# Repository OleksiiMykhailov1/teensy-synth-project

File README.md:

# Teensy synth project

_Listen on YouTube_

This is a project I was working on in 2023. My main goal was to create an interesting object to interact with while learning about software and hardware development. Before starting it, 
I did some small projects with Arduino and assembled a small analogue synth with 3 voices and a low-pass filter. I found the programming part more interesting to me, and it allowed more to be done.
Teensy 3.6 was chosen because it works with the Audio Library and Audio Systems Design Tool, which allow me to work on system design while relying on a professionally written DSP and an easy-to-use design tool to create an audio patch for my synthesizer.
The first version of the project was soldered on a perfboard, as a proof of concept. It worked, so I decided to try to design and manufacture a PCB.

_Perfboard and a PCB versions_

## Hardware
 
| Part | Details |
|------|---------|
| Microcontroller | Teensy 3.6 |
| Display | ILI9341 TFT (320×240, landscape) |
| Keypad | 5×4 matrix of Kailh Choc V1 Low Profile Switches |
| Rotary encoder | to navigate through the menu |
| Audio out | USB audio; the SGTL5000 codec on board was not working, and I was not able to find out why at the time |
| Power | powered through USB |

## Features
 
- **4-voice polyphony**, with 4 operators per voice 
- **11 FM algorithms**, selectable from the display
- **Per-operator controls:** waveform (sine/triangle/square), frequency ratio, level and a full ADSR envelope
- **Effects chain:** low-pass filter with LFO, multi-tap delay with feedback, and Freeverb reverb, each with its own wet/dry mix
- **Step Sequencer:** up to 32 steps, with rests and adjustable BPM
- **On-screen feedback:** algorithm diagram, envelope graphs for every operator and a live output waveform

## How it works
Each voice has 4 operators, each a frequency-modulated oscillator followed by its own ADSR envelope. A mixer in front of every oscillator chooses which operators modulate it.
Then the signal goes through the voice mixer, through the effects, and to one of the outputs.

### Keypad layout
 
 | | Col 1 | Col 2 | Col 3 | Col 4 | Col 5 |
|---|:---:|:---:|:---:|:---:|:---:|
| **Row 1** | Edit / confirm | F♯  | D♯ | C♯| Next |
| **Row 2** | F| E | D | C | Back |
| **Row 3** |Seq play/stop | C♯(+1 oct) | A♯ |  G♯ | - |
| **Row 4** |  C (+1 oct) | B | A  | G | - |

- **Notes:** up to 4 notes can sound at once; each new note takes the next free voice.
- **Next / Back:** switch screens, or step through parameters while editing.
- **Edit / confirm:** enter or leave editing for the highlighted item.
- **Seq play/stop:** starts or stops the sequencer from any screen.
  
### Screens

Use **Next / Back** (when not editing) to move between screens.
 
**1. Synth.** Turn the encoder to highlight **OCT**, **ALG** or **OP-1 … OP-4**, then press **Edit** to change it.
For an operator, **Next / Back** step through the parameter being edited, and the encoder changes its value:
 
| Parameter | Range |
|-----------|-------|
| Attack | 0–1000 ms |
| Decay | 0–1000 ms |
| Sustain | 0.0–1.0 |
| Release | 0–3800 ms |
| Ratio | 0–16 (frequency multiple of the played note) |
| Level | 0.0–1.0 |
| Waveform | sine / triangle / square |
 
**2. Effects.** Pick **Reverb**, **Delay** or **Filter** with the encoder, press **Edit**, use **Next / Back** to move the arrow between parameters and the encoder to change them:
 
| Block | Parameters |
|-------|------------|
| Reverb | room size (0–1), damping (0–1), wet/dry |
| Delay | taps (0–3), time (10–500 ms), feedback (0–0.5), wet/dry |
| Filter | cutoff (0–5000 Hz), resonance, wet/dry, LFO rate (0–50 Hz) |
 
**3. Step Sequencer.** Pick **Record**, **Steps** or **BPM** with the encoder:
 
- **Record:** press **Edit** to start/stop recording. Play notes to write them into the sequence; **Next / Back** write a rest.
- **Steps:** sequence length, 1–32.
- **BPM:** tempo of the step clock.
- The Sequencer plays on a single voice (monophonic).

### Project problems

- SGTL5000 codec. While I was working on a project, there was a chip shortage, and I was only able to buy it from a sketchy AliExpress supplier. Either this or my poor, at the time, soldering skills, I was not able to make it work, and USB was the only audio output that was working.
- Code. It was my first attempt to do something complex. I had no experience and made a lot of bad design choices, but it somehow works, which is cool.
- PCB. Besides a problem with a codec, it's also my first PCB, routing is bad and probably anyone with any experience will find a lot of mistakes.

### Planned upgrades

At some point, I decided that the PCB needs serious upgrades, and there is no point in continuing to write code if I will make major changes to the hardware.
You can see files for the upgraded PCB in [`PCB files/teensy_4_1_pcb/`](PCB%20files/teensy_4_1_pcb/).
What was made:
- I decided to switch from a display module to a bare screen. It allowed me to reduce the synth's size.
- I removed 5 keys. In the last design, part of the keys were not used at all, which again reduced the size.
- SGTL5000 was changed to PT8211, it's easier to use, cheaper, and good enough for my tasks.
- Added battery support. I copied this part of the schematic from another synth that used a Teensy.

This board was never manufactured. At the time, I changed jobs, and there was no time to continue work on it.

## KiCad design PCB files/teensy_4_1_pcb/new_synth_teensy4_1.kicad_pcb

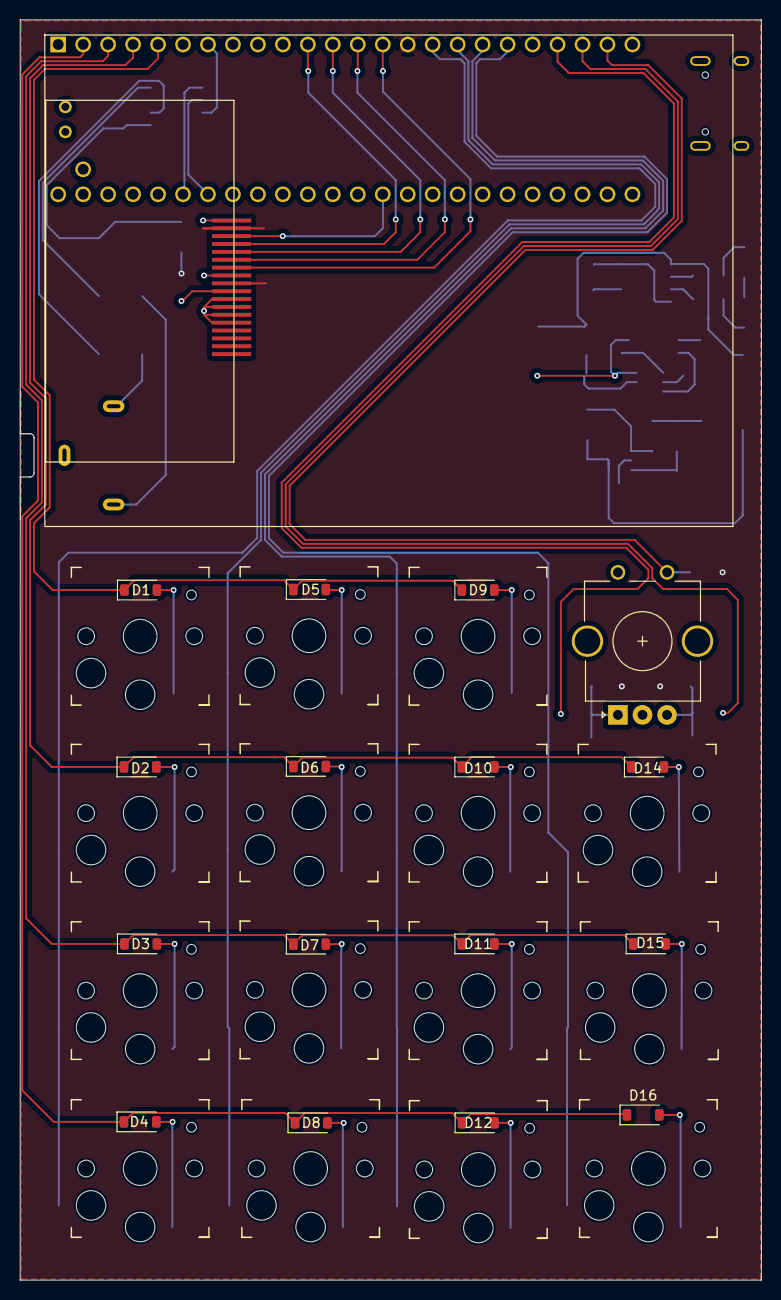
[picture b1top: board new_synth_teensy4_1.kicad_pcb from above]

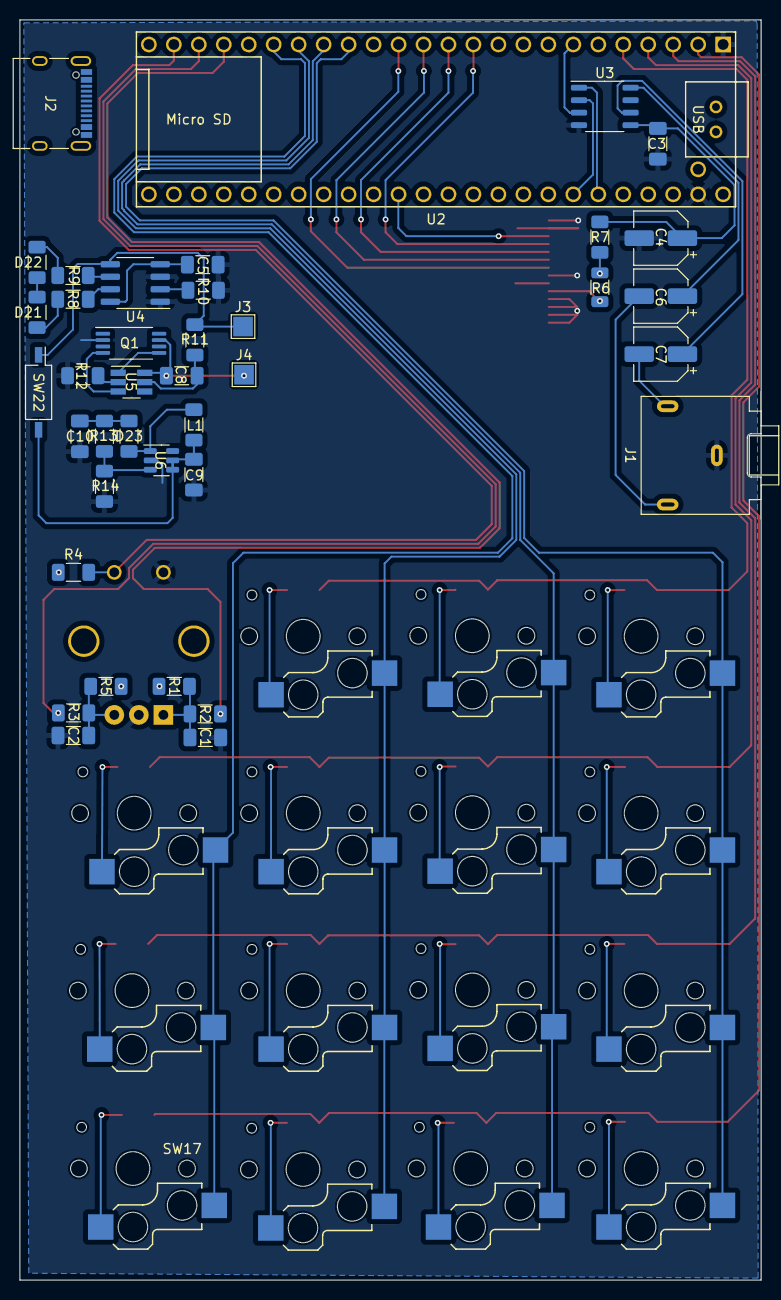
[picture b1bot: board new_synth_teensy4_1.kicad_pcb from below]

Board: 2 copper layers, 75.4 x 128.2 mm, 71 parts (39 on the bottom side), 61 nets.

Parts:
C1, C2: 100nF; C_1206_3216Metric_Pad1.33x1.80mm_HandSolder
C3: 0.1uF; C_1206_3216Metric_Pad1.33x1.80mm_HandSolder
C4, C6, C7: 47uF; CP_Elec_5x5.8
C5: 10uf; C_1206_3216Metric_Pad1.33x1.80mm_HandSolder
C8: 0.1uf; C_1206_3216Metric_Pad1.33x1.80mm_HandSolder
C9, C10: 22uf; C_1206_3216Metric_Pad1.33x1.80mm_HandSolder
D1, D2, D3, D4, D5, D6, D7, D8, D9, D10, D11, D12, D14, D15, D16: 1N4001; D_SOD-123
D21: RED; R_1206_3216Metric_Pad1.30x1.75mm_HandSolder
D22: GREEN; R_1206_3216Metric_Pad1.30x1.75mm_HandSolder
D23: D_Schottky; R_1206_3216Metric_Pad1.30x1.75mm_HandSolder
J1: AudioJack2_Ground; Jack_3.5mm_CUI_SJ1-3523N_Horizontal
J2: USB_B_Micro; USB_C_Receptacle_XKB_U262-16XN-4BVC11
J3: BAT+ Pad; TestPoint_Pad_2.0x2.0mm
J4: BAT- Pad; TestPoint_Pad_2.0x2.0mm
L1: 22UH; R_1206_3216Metric_Pad1.30x1.75mm_HandSolder
Q1: TSSOP-8_4.4x3mm_P0.65mm
R1, R2, R3, R4, R5: 10K; R_1206_3216Metric_Pad1.30x1.75mm_HandSolder
R6: 1k?; R_1206_3216Metric
R7: 10R; R_1206_3216Metric_Pad1.30x1.75mm_HandSolder
R8, R9: 1K; R_1206_3216Metric_Pad1.30x1.75mm_HandSolder
R10, R12: 2K; R_1206_3216Metric_Pad1.30x1.75mm_HandSolder
R11: r100; R_1206_3216Metric_Pad1.30x1.75mm_HandSolder
R13: 7.5k; R_1206_3216Metric_Pad1.30x1.75mm_HandSolder
R14: 1k; R_1206_3216Metric_Pad1.30x1.75mm_HandSolder
SW1: RotaryEncoder_Switch; RotaryEncoder_Alps_EC11E_Vertical_H20mm_CircularMountingHol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
SW2, SW3, SW4, SW5, SW6, SW7, SW8, SW9, SW10, SW11, SW12, SW13, SW15, SW16, SW17: SW_Push; Kailh_socket_PG1350
SW22: SW_DIP_x01; SW_DIP_SPSTx01_Slide_Copal_CHS-01B_W7.62mm_P1.27mm
U2: Teensy4.1; Teensy41
U3: SOP-8_3.9x4.9mm_P1.27mm
U4: TP4056; SOP-8_3.76x4.96mm_P1.27mm
U5: SOT-23-6_Handsoldering
U6: MT3608; SOT-23-6
U7: ILI9341_BARE_18PIN

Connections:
5V BAT: C10.2, D23.1 (K), R13.2
+3.3V: R1.2, R4.1, R5.1, R6.1, R7.2, U2.15 (3V3), U7.2 (Reset), U7.9 (VCC)
DIN: U2.7 (5_IN2), U3.3 (DIN)
GND: C1.2, C2.1, C3.2, C4.2, C5.2, C9.1, C10.1, J1.G, Q1.2 (S1), R10.1, R12.1, R14.1, SW1.C, SW1.S1, U2.1 (GND), U2.47 (GND), U3.4 (GND), U4.1 (Temp), U4.3 (GND), U6.2 (GND), U7.1 (GND), U7.8 (GND), U7.11 (K1(LED_Cathode)), U7.12 (K2(LED_Cathode)), U7.13 (K3(LED_Cathode)), U7.14 (K4(LED_Cathode))
unnamed: C1.1, R1.1, R2.2, SW1.A
unnamed: C2.2, R3.2, R5.2, SW1.B
unnamed: C6.2, J1.S
unnamed: C7.2, J1.T
unnamed: D1.2 (A), SW2.1
unnamed: D1.1 (K), D5.1 (K), D9.1 (K), U2.5 (3_LRCLK2)
unnamed: D2.2 (A), SW3.1
unnamed: D3.2 (A), SW4.1
unnamed: D4.2 (A), SW5.1
unnamed: D5.2 (A), SW6.1
unnamed: D6.2 (A), SW7.1
unnamed: D7.2 (A), SW8.1
unnamed: D8.2 (A), SW9.1
unnamed: D9.2 (A), SW10.1
unnamed: D10.2 (A), SW11.1
unnamed: D2.1 (K), D6.1 (K), D10.1 (K), D14.1 (K), U2.4 (2_OUT2)
unnamed: D11.2 (A), SW12.1
unnamed: D3.1 (K), D7.1 (K), D11.1 (K), D15.1 (K), U2.3 (1_TX1_CTX2_MISO1)
unnamed: D12.2 (A), SW13.1
unnamed: D4.1 (K), D8.1 (K), D12.1 (K), D16.1 (K), U2.2 (0_RX1_CRX2_CS1)
unnamed: D14.2 (A), SW15.1
unnamed: D15.2 (A), SW16.1
unnamed: D16.2 (A), SW17.1
unnamed: D21.2 (A), D22.2 (A)
unnamed: D21.1 (K), R8.2
unnamed: D22.1 (K), R9.2
unnamed: D23.2 (A), L1.2, U6.1 (SW)
unnamed: C5.1, U4.4 (VCC), U4.8 (CE)
unnamed: J3.1, R11.1, SW22.1, U4.5 (BAT)
unnamed: C8.1, J4.1, Q1.7 (S2), U5.6 (GND)
unnamed: Q1.4 (G1), U5.3 (OC)
unnamed: Q1.5 (G2), U5.1 (OD)
unnamed: U2.11 (9_OUT1C), U7.4 (DC/RS)
unnamed: U2.12 (10_CS_MQSR), U7.5 (CS)
unnamed: U2.13 (11_MOSI_CTX1), U7.6 (SDA(MOSI))
unnamed: U2.14 (12_MISO_MQSL), U7.7 (SDO(MISO))
unnamed: U2.42 (20_A6_TX5_LRCLK1), U3.2 (WS)
unnamed: U2.43 (21_A7_RX5_BCLK1), U3.1 (BCK)
unnamed: SW2.2, SW3.2, SW4.2, SW5.2, U2.16 (24_A10_TX6_SCL2)
unnamed: SW6.2, SW7.2, SW8.2, SW9.2, U2.17 (25_A11_RX6_SDA2)
unnamed: SW10.2, SW11.2, SW12.2, SW13.2, U2.18 (26_A12_MOSI1)
unnamed: SW15.2, SW16.2, SW17.2, U2.19 (27_A13_SCK1)
unnamed: R2.1, U2.21 (29_TX7)
unnamed: R3.1, U2.22 (30_CRX3)
unnamed: R4.2, SW1.S2, U2.23 (31_CTX3)
unnamed: C3.1, C4.1, R7.1, U3.5 (3.3)
unnamed: C7.1, U3.6 (LLCH)
unnamed: C6.1, U3.8 (RCH)
unnamed: R8.1, U4.7 (CHRG)
unnamed: R10.2, U4.2 (Prog)
unnamed: R9.1, U4.6 (STDBY)
unnamed: R12.2, U5.2 (CS)
unnamed: C8.2, R11.2, U5.5 (VCC)
unnamed: C9.2, L1.1, SW22.2, U6.4 (EN), U6.5 (IN)
unnamed: R13.1, R14.2, U6.3 (FB)
unnamed: R6.2, U7.10 (A(LED_Anode))
SCK: U2.35 (13_SCK_LED), U7.3 (SCL)

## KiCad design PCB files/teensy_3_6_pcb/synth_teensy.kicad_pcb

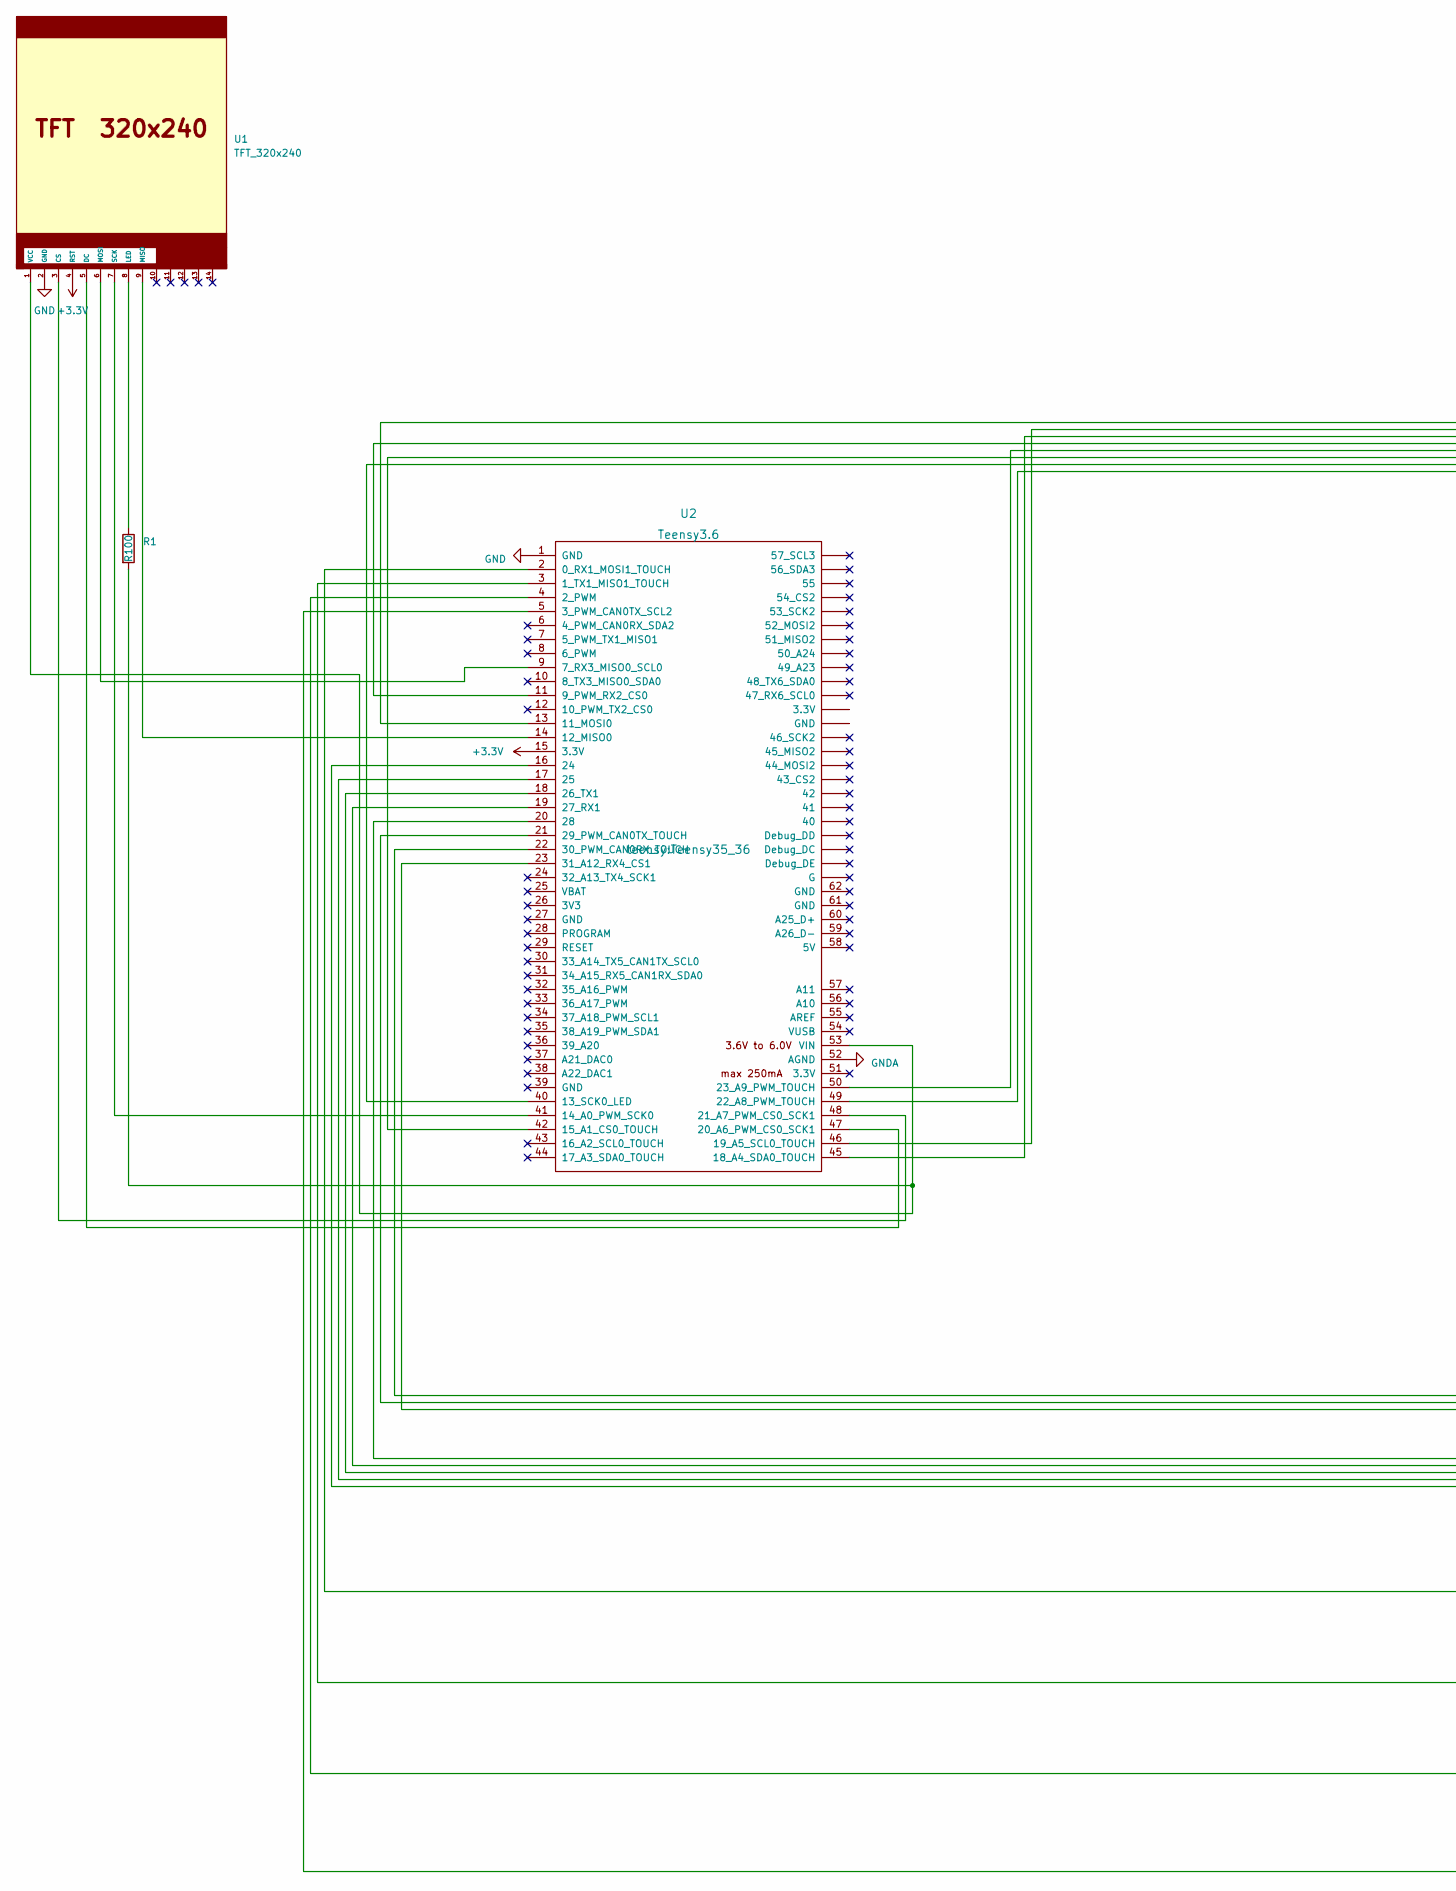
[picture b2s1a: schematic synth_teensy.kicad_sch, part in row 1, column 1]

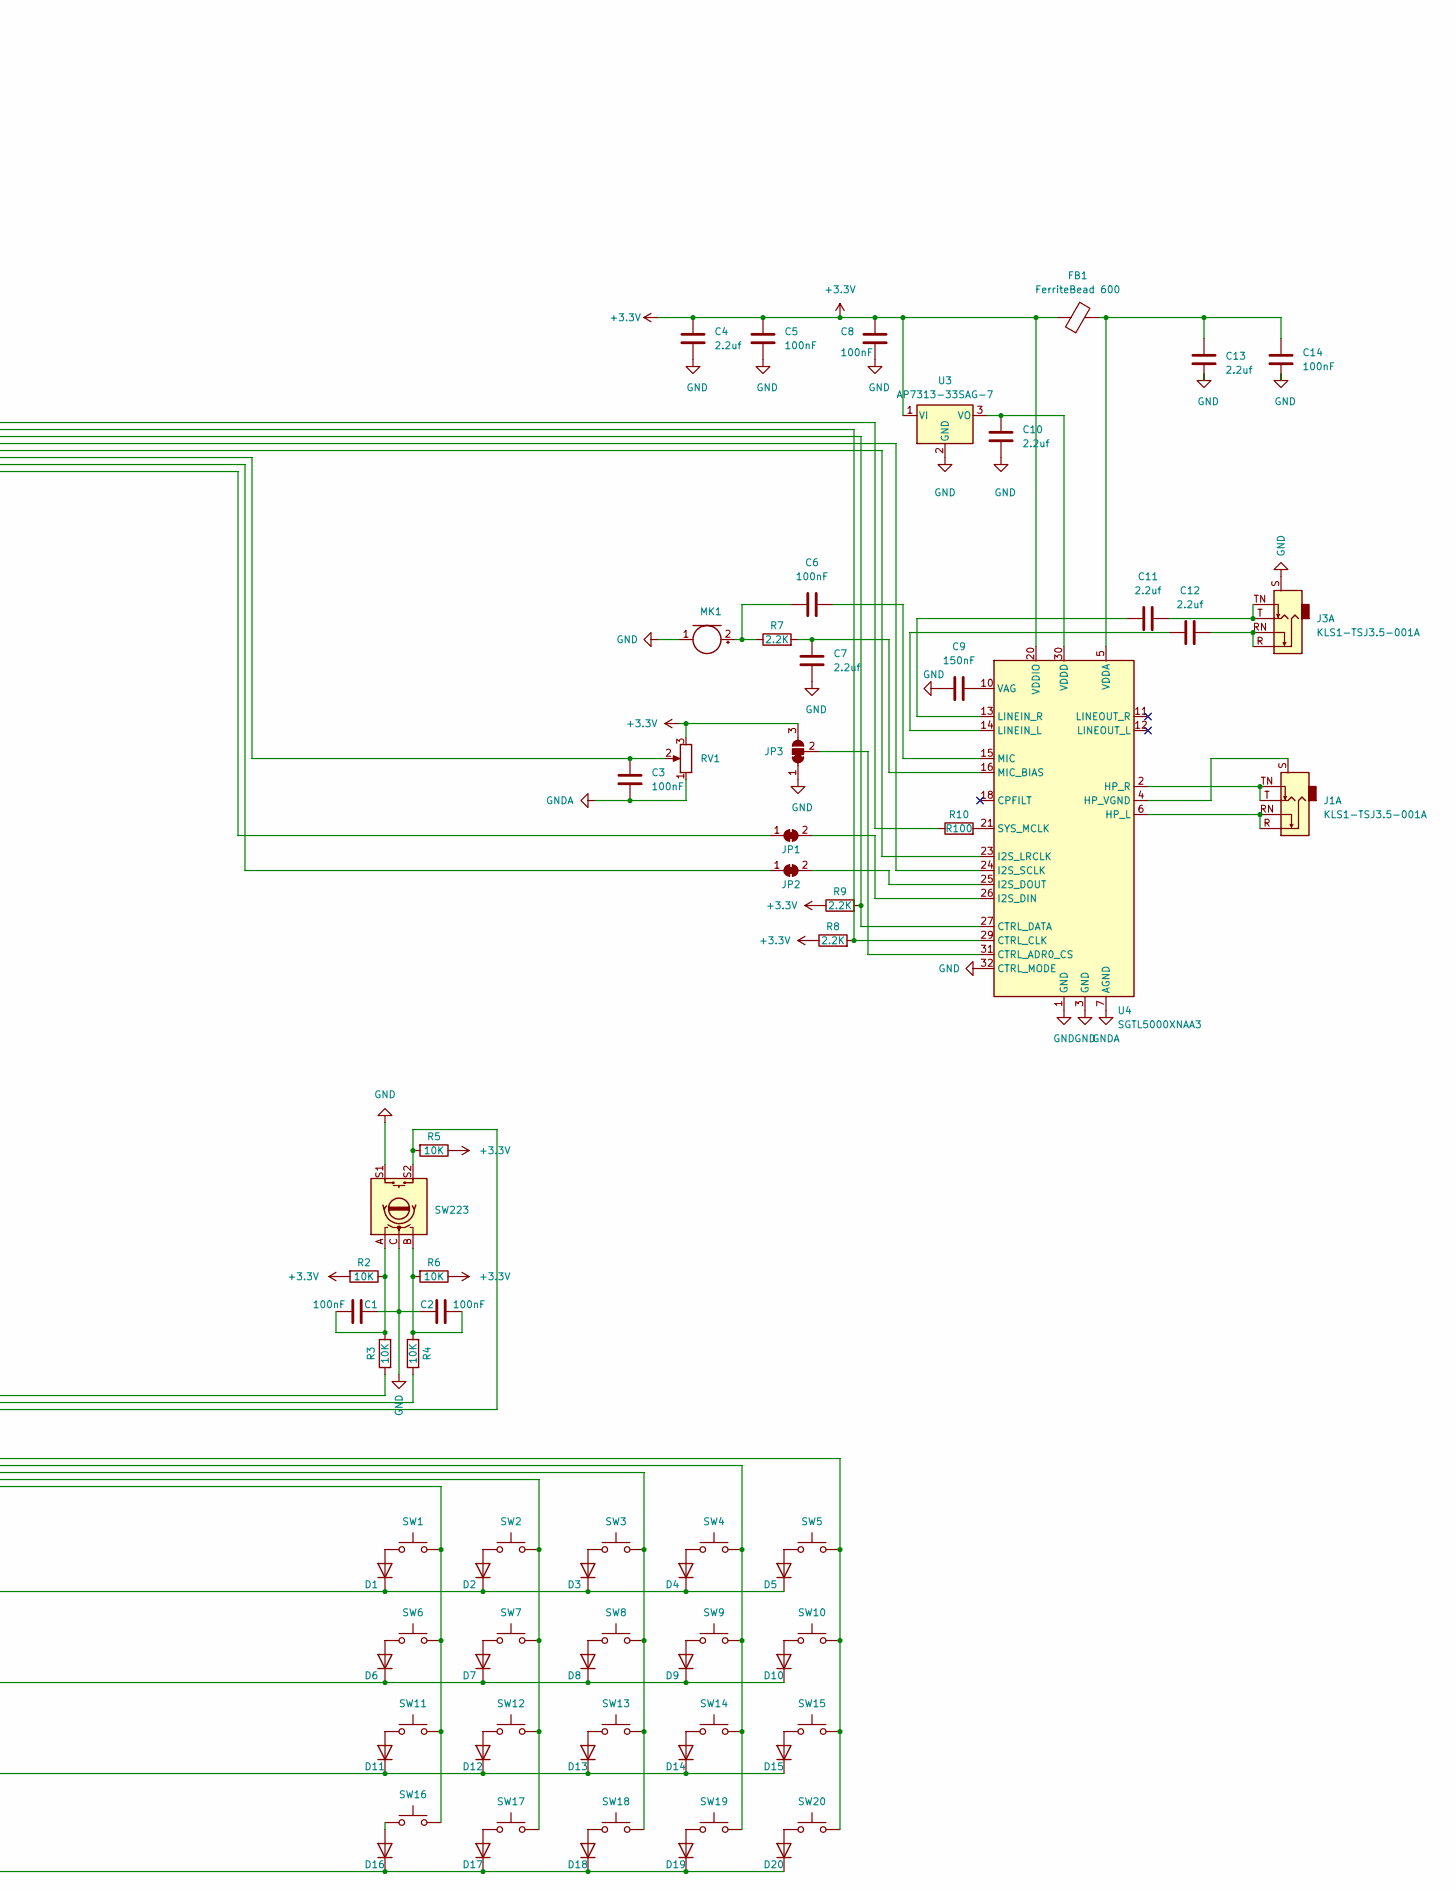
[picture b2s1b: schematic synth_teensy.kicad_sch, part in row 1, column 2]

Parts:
C1, C2, C3, C5, C6, C8, C14: 100nF; C_1206_3216Metric_Pad1.33x1.80mm_HandSolder
C4, C7, C10, C11, C12, C13: 2.2uf; C_1206_3216Metric_Pad1.33x1.80mm_HandSolder
C9: 150nF; C_1206_3216Metric_Pad1.33x1.80mm_HandSolder
D1, D2, D3, D4, D5, D6, D7, D8, D9, D10, D11, D12, D13, D14, D15, D16, D17, D18, D19, D20: 1N4001; D_1210_3225Metric
FB1: FerriteBead 600; R_1206_3216Metric_Pad1.30x1.75mm_HandSolder
J1, J3: KLS1-TSJ3.5-001A; Jack_3.5mm_CUI_SJ1-3525N_Horizontal
JP1, JP2: SolderJumper_2_Bridged; SolderJumper-2_P1.3mm_Bridged_RoundedPad1.0x1.5mm
JP3: SolderJumper_3_Bridged12; SolderJumper-3_P1.3mm_Bridged12_RoundedPad1.0x1.5mm_NumberL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
MK1: Microphone; R_Axial_DIN0411_L9.9mm_D3.6mm_P12.70mm_Horizontal
R1, R10: R100; R_1206_3216Metric_Pad1.30x1.75mm_HandSolder
R2, R3, R4, R5, R6: 10K; R_1206_3216Metric_Pad1.30x1.75mm_HandSolder
R7, R8, R9: 2.2K; R_1206_3216Metric_Pad1.30x1.75mm_HandSolder
RV1: R_Potentiometer; Potentiometer_Alps_RK09Y11_Single_Horizontal
SW1, SW2, SW3, SW4, SW5, SW6, SW7, SW8, SW9, SW10, SW11, SW12, SW13, SW14, SW15, SW16, SW17, SW18, SW19, SW20: SW_Push; Kailh_socket_PG1350
SW223: RotaryEncoder_Switch; RotaryEncoder_Alps_EC11E_Vertical_H20mm_CircularMountingHol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
U1: TFT_320x240; TFT-320x240
U2: Teensy3.6; Teensy35_36
U3: AP7313-33SAG-7; SOT-23-3
U4: SGTL5000XNAA3; QFN-32-1EP_5x5mm_P0.5mm_EP3.6x3.6mm

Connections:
+3V3: C4.1, C5.1, C8.1, FB1.1, JP3.3 (B), R2.2, R5.1, R6.1, R8.1, R9.1, RV1.3, U1.4 (RST), U2.15 (3.3V), U3.1 (VI), U4.20 (VDDIO); also elsewhere on the board
GNDA: C3.2, RV1.1, U2.52 (AGND), U4.7 (AGND); also elsewhere on the board
unnamed: C1.1, R2.1, R3.2, SW223.A
unnamed: C2.2, R4.2, R6.2, SW223.B
unnamed: C11.2, J3.T, J3.TN
unnamed: C12.2, J3.R, J3.RN
unnamed: D1.2 (A), SW1.1
unnamed: D1.1 (K), D2.1 (K), D3.1 (K), D4.1 (K), D5.1 (K), U2.2 (0_RX1_MOSI1_TOUCH)
unnamed: D2.2 (A), SW2.1
unnamed: D3.2 (A), SW3.1
unnamed: D4.2 (A), SW4.1
unnamed: D5.2 (A), SW5.1
unnamed: D6.2 (A), SW6.1
unnamed: D7.2 (A), SW7.1
unnamed: D8.2 (A), SW8.1
unnamed: D9.2 (A), SW9.1
unnamed: D10.2 (A), SW10.1
unnamed: D6.1 (K), D7.1 (K), D8.1 (K), D9.1 (K), D10.1 (K), U2.3 (1_TX1_MISO1_TOUCH)
unnamed: D11.2 (A), SW11.1
unnamed: D11.1 (K), D12.1 (K), D13.1 (K), D14.1 (K), D15.1 (K), U2.4 (2_PWM)
unnamed: D12.2 (A), SW12.1
unnamed: D13.2 (A), SW13.1
unnamed: D14.2 (A), SW14.1
unnamed: D15.2 (A), SW15.1
unnamed: D16.2 (A), SW16.1
unnamed: D16.1 (K), D17.1 (K), D18.1 (K), D19.1 (K), D20.1 (K), U2.5 (3_PWM_CAN0TX_SCL2)
unnamed: D17.2 (A), SW17.1
unnamed: D18.2 (A), SW18.1
unnamed: D19.2 (A), SW19.1
unnamed: D20.2 (A), SW20.1
unnamed: JP1.1 (A), U2.49 (22_A8_PWM_TOUCH)
unnamed: JP1.2 (B), U4.26 (I2S_DIN)
unnamed: JP2.1 (A), U2.40 (13_SCK0_LED)
unnamed: JP2.2 (B), U4.25 (I2S_DOUT)
unnamed: JP3.2 (C), U4.31 (CTRL_ADR0_CS)
unnamed: C6.1, MK1.2 (+), R7.1
unnamed: U1.3 (CS), U2.48 (21_A7_PWM_CS0_SCK1)
unnamed: U1.5 (DC), U2.47 (20_A6_PWM_CS0_SCK1)
unnamed: R1.1, U1.8 (LED)
unnamed: U1.9 (MISO), U2.14 (12_MISO0)
unnamed: U1.6 (MOSI), U2.9 (7_RX3_MISO0_SCL0)
unnamed: U1.7 (SCK), U2.41 (14_A0_PWM_SCK0)
unnamed: R1.2, U1.1 (VCC), U2.53 (VIN)
unnamed: U2.11 (9_PWM_RX2_CS0), U4.24 (I2S_SCLK)
unnamed: R10.1, U2.13 (11_MOSI0)
unnamed 45: C3.1, RV1.2, U2.42 (15_A1_CS0_TOUCH); also elsewhere on the board
unnamed: R9.2, U2.45 (18_A4_SDA0_TOUCH), U4.27 (CTRL_DATA)
unnamed: R8.2, U2.46 (19_A5_SCL0_TOUCH), U4.29 (CTRL_CLK)
unnamed: U2.50 (23_A9_PWM_TOUCH), U4.23 (I2S_LRCLK)
unnamed: SW1.2, SW6.2, SW11.2, SW16.2, U2.16 (24)
unnamed: SW2.2, SW7.2, SW12.2, SW17.2, U2.17 (25)
unnamed: SW3.2, SW8.2, SW13.2, SW18.2, U2.18 (26_TX1)
unnamed: SW4.2, SW9.2, SW14.2, SW19.2, U2.19 (27_RX1)
unnamed: SW5.2, SW10.2, SW15.2, SW20.2, U2.20 (28)
unnamed: R4.1, U2.21 (29_PWM_CAN0TX_TOUCH)
unnamed: R3.1, U2.22 (30_PWM_CAN0RX_TOUCH)
unnamed: R5.2, SW223.S2, U2.23 (31_A12_RX4_CS1)
unnamed: J1.R, J1.RN, U4.6 (HP_L)
unnamed: J1.T, J1.TN, U4.2 (HP_R)
unnamed: J1.S, U4.4 (HP_VGND)
unnamed: C12.1, U4.14 (LINEIN_L)
unnamed: C11.1, U4.13 (LINEIN_R)
unnamed: C6.2, U4.15 (MIC)
unnamed: C7.2, R7.2, U4.16 (MIC_BIAS)
unnamed: R10.2, U4.21 (SYS_MCLK)
unnamed: C9.2, U4.10 (VAG)
unnamed: C13.1, C14.1, FB1.2, U4.5 (VDDA)

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
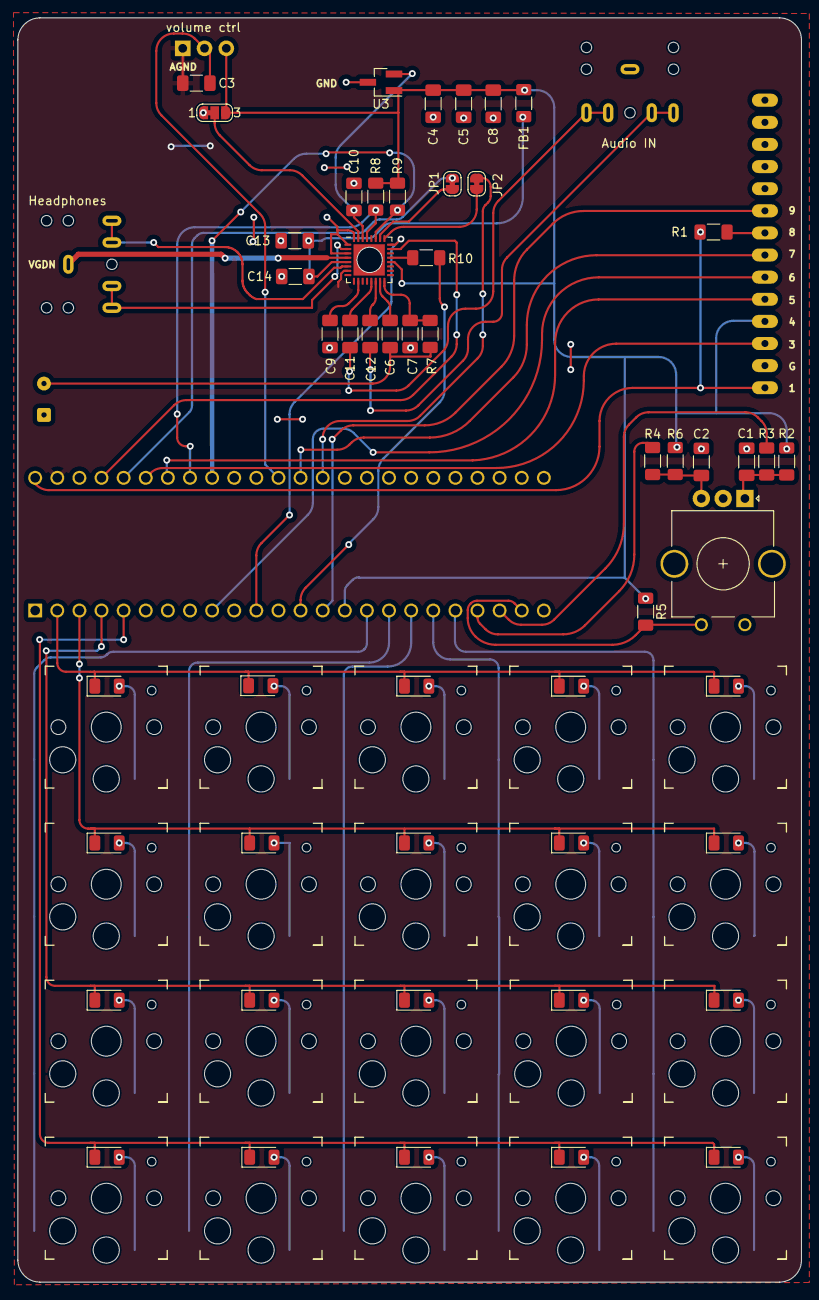
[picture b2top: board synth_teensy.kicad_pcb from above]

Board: 2 copper layers, 90.0 x 145.2 mm, 77 parts (0 on the bottom side), 69 nets.

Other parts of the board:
volume ctrl: R_Potentiometer; Potentiometer_Alps_RK09Y11_Single_Horizontal

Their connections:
+3V3: volume ctrl.3; also elsewhere on the board
GNDA: volume ctrl.1; also elsewhere on the board
unnamed 45: volume ctrl.2; also elsewhere on the board
